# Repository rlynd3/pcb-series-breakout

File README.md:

# pcb-series-breakout
Breakout board for battery series connection

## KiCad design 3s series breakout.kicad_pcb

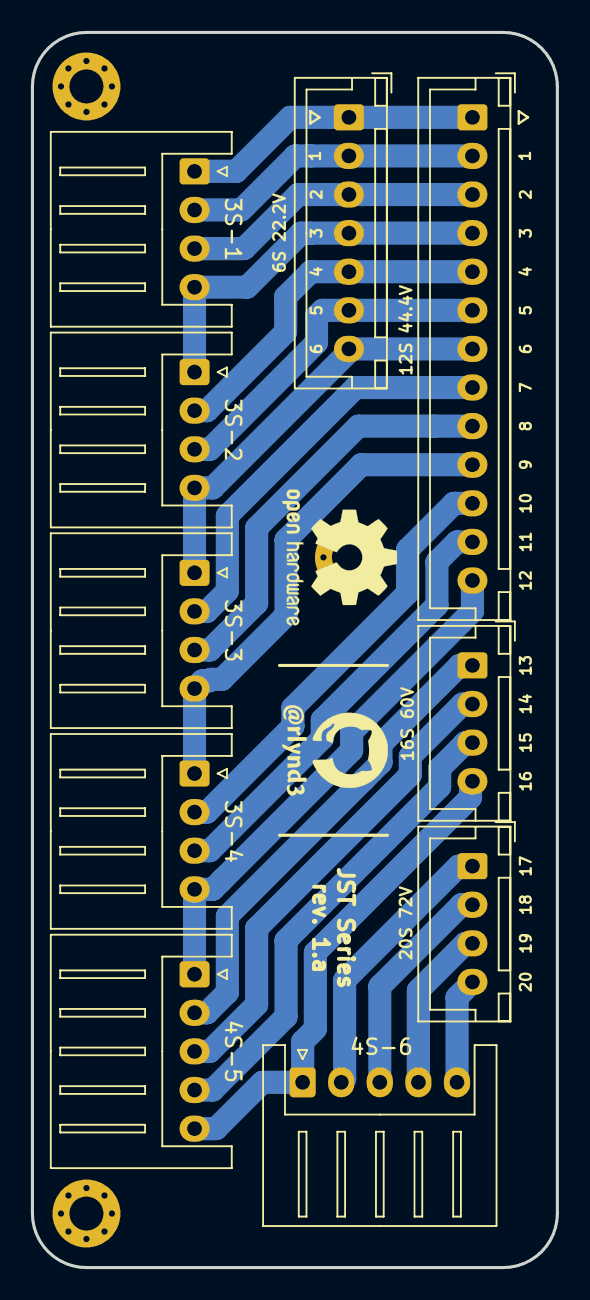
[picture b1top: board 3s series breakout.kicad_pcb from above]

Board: 2 copper layers, 34.0 x 80.0 mm, 13 parts (0 on the bottom side), 21 nets.

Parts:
3S-1, 3S-2, 3S-3, 3S-4: JST XH 3S; JST_XH_S04B-XH-A_1x04_P2.50mm_Horizontal
4S-5, 4S-6: JST XH 4S; JST_XH_S05B-XH-A_1x05_P2.50mm_Horizontal
6S1: JST XH 6S; JST_XH_B07B-XH-A_1x07_P2.50mm_Vertical
12S-A1: JST XH 12s; JST_XH_B13B-XH-A_1x13_P2.50mm_Vertical
16S-B1: JST XH 16S-B; JST_XH_B04B-XH-A_1x04_P2.50mm_Vertical
20S-C1: JST XH 20S-B; JST_XH_B04B-XH-A_1x04_P2.50mm_Vertical
M1, M2, M3: MountingHole_2.2mm_M2_Pad_Via

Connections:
unnamed: 3S-1.1, 6S1.1, 12S-A1.1
unnamed: 3S-1.2, 6S1.2, 12S-A1.2
unnamed: 3S-1.3, 6S1.3, 12S-A1.3
unnamed: 3S-1.4, 3S-2.1, 6S1.4, 12S-A1.4
unnamed: 3S-2.2, 6S1.5, 12S-A1.5
unnamed: 3S-2.3, 6S1.6, 12S-A1.6
unnamed: 3S-2.4, 3S-3.1, 6S1.7, 12S-A1.7
unnamed: 3S-3.2, 12S-A1.8
unnamed: 3S-3.3, 12S-A1.9
unnamed: 3S-3.4, 3S-4.1, 12S-A1.10
unnamed: 3S-4.2, 12S-A1.11
unnamed: 3S-4.3, 12S-A1.12
unnamed: 3S-4.4, 4S-5.1, 12S-A1.13
unnamed: 4S-5.2, 16S-B1.1
unnamed: 4S-5.3, 16S-B1.2
unnamed: 4S-5.4, 16S-B1.3
unnamed: 4S-5.5, 4S-6.1, 16S-B1.4
unnamed: 4S-6.2, 20S-C1.1
unnamed: 4S-6.3, 20S-C1.2
unnamed: 4S-6.4, 20S-C1.3
unnamed: 4S-6.5, 20S-C1.4

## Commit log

2019-01-12 add logos and fix up most labels
2019-01-13 clean up labels
2019-01-13 add images and clean-up labels
